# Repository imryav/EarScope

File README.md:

# EarScope — In-Ear Bio-Acoustic Cardiac Monitor (Seeed Studio XIAO RA4M1 Edition)

**EarScope** is an ultra-low-noise, compact hardware and software acquisition platform that captures acoustic and micro-mechanical cardiac biosignals (**PCG**, **SCG**, and **GCG**) directly from an occluded ear canal using standard wired earphones (`3.5 mm` AUX), inspired by *LubDubDecoder (ACM CHI '26)*.

> **Project Engineering Documentation & Hardware Files:**
> * **[Turnkey PCB Fabrication & JLCPCB PCBA Package (`fabrication_files/`)](fabrication_files/)** — Ready-to-order Gerber/Drill ZIP ([`EarScope_XIAO_RA4M1_Gerbers_JLCPCB.zip`](fabrication_files/EarScope_XIAO_RA4M1_Gerbers_JLCPCB.zip)), unpacked RS-274X Gerbers + Excellon Drills, LCSC BOM + CPL CSVs, and ordering guide.
> * **[LTspice Finalization, Verification & Simulation Results](docs/ltspice_simulation_guide.md)** — Validated `3.30 V` cardiac AFE + `1.58 kHz` USB power-supply LPF schematic ([`AFE_Cardiac_5-45Hz.asc`](docs/AFE_Cardiac_5-45Hz.asc) + [`OPA365.lib`](docs/OPA365.lib)), rationale, and verification plots.
> * **[Fabrication-Ready KiCad 8 / 9 Project (`hardware_pcb/EarScope_XIAO_RA4M1/`)](hardware_pcb/EarScope_XIAO_RA4M1/)** — Complete editable schematic (`.kicad_sch`), `100%` routed `48.0 × 20.0 mm` 2-layer PCB (`.kicad_pcb`), and custom footprint library (`.pretty`).
> * **[KiCad 8 / 9 Integrated SPICE (`ngspice`) Simulation Guide & 1-Click Testbench](docs/kicad_spice_simulation_guide.md)** — Ready-to-run KiCad SPICE project ([`hardware_pcb/EarScope_SPICE_Sim/`](hardware_pcb/EarScope_SPICE_Sim/) with [`OPA2365_Dual.lib`](hardware_pcb/EarScope_SPICE_Sim/OPA2365_Dual.lib)) + step-by-step `OP`, `AC` Bode, and `TRAN` verification instructions.
> * **[`kicad-happy` Automated Design Review & Fabrication Release Gate (`11/11 PASS`)](docs/kicad_happy_design_review.md)** — Full electrical, Gerber/CAM, DFM (`0` violations), and EMC (`100 / 100`) sign-off via [`aklofas/kicad-happy`](https://github.com/aklofas/kicad-happy).
> * **[KiCad 8 / 9 Schematic & PCB Design Guide](docs/kicad_pcb_design_guide.md)** — Complete symbol/footprint mapping, custom castellated XIAO RA4M1 footprint with underside pad keepout, `48.0 × 20.0 mm` 2-layer layout, `1.58 kHz` USB LPF, `JP1` solder jumper, active `VREF` guard ring, and Gerber export.
> * **[Enclosure & Carrier PCB Co-Design Guide](docs/fusion360_enclosure_guide.md)** — Parametric Fusion 360 snap-fit enclosure co-designed for the `48.0 × 20.0 mm` XIAO RA4M1 carrier PCB.

---

## 1. System Architecture Overview

EarScope converts microscopic tympanic/ear-canal pressure oscillations (`5 Hz – 45 Hz`) into a high-resolution digital stream over **USB-C**:

* **Sensor Input (`3.5 mm` AUX `PJ-320A` + `JP1` SMD Solder Jumper):** Supports standard passive dynamic earphones (`16–32 Ω` voice coil operating in reverse as a zero-bias acoustic transducer via the ear-canal occlusion effect) **and** electret microphone capsules via a compact 2-pad SMD solder jumper (**`JP1: OPEN = EAR / BRIDGE = MIC`**, switching `2.2 kΩ` DC bias from `+3V3_ANA` with zero mechanical switch contact bounce or enclosure side cutout).
* **Cardiac Analog Front-End (`OPA2365` × 2):** Dual ultra-low-noise (`4.5 nV/√Hz`), rail-to-rail CMOS operational amplifiers configured as a breathing-protected `53.2 dB` preamplifier followed by a 4th-order Butterworth `5 Hz – 45 Hz` bandpass filter (`-60 dB/decade` sub-cardiac slope including input coupling).
* **Two-Stage Quiet `3.30 V` Analog Power Island (`1.58 kHz` Pre-LPF + Low-Noise LDO):** Noisy `+5V_USB` power first passes through a dedicated passive RC Low-Pass Filter (**`R13 = 10 Ω`** feeding **`+5V_FILT`** decoupled by **`C9 = 10 µF` || `C13 = 100 nF`**, $f_c = 1.576\text{ kHz}$, providing `~56 dB` high-frequency USB switching rejection at `1 MHz` where LDO PSRR degrades) before `U3` (`MCP1700T-3302E/TT`) regulates a clean **`3.300 V`** analog rail (`+3V3_ANA`) and **`1.650 V`** virtual-ground reference.
* **Thumb-Sized Digital Acquisition & Streaming (`Seeed Studio XIAO RA4M1` / `102010551`):** Powered by the **Renesas `RA4M1`** (`R7FA4M1AB3CFM`, `48 MHz` Arm Cortex-M4F with FPU) in a `21.0 × 17.8 mm` 14-pad castellated SMD footprint, shrinking the carrier PCB by `29.4%` (`48.0 × 20.0 mm`) while sampling at `500 Hz` with a **true 14-bit SAR ADC** (`0–16,383` counts, `1 LSB = 201.4 µV`) and zero Wi-Fi/BLE RF burst interference over onboard **USB-C**.

```text
[Earphones / Mic (3.5mm AUX + JP1)] ---> [Cardiac AFE (OPA2365, 5–45Hz, USB LPF + 3.30V LDO)] ---> [Seeed XIAO RA4M1 14-Bit ADC (Pin D1/A1)] ===(USB-C @ 500Hz)===> [PC / Python UI]
```

---

## 2. Target Physiological Signals

1. **Phonocardiography (PCG):** Audible and sub-audible heart valve closure sounds (`S1` *"Lub"* and `S2` *"Dub"*).
2. **Seismocardiography (SCG) & Gyrocardiography (GCG):** Reconstruction of chest-wall micro-mechanical cardiac vibrations coupled acoustically through the vasculature and skull into the sealed ear canal.
3. **Cardiac Fiducial Timing Landmarks:**
   * **MC** — Mitral Valve Closure
   * **IM** — Isovolumetric Moment
   * **AO** — Aortic Valve Opening
   * **MA** — Maximal Acceleration
   * **RE** — Rapid Ejection

---

## 3. Finalized Analog Front-End (AFE) & Power Filtering Design

The production schematic (`AFE_Cardiac_5-45Hz.asc` & `EarScope_XIAO_RA4M1.kicad_sch`) comprises six tightly coordinated analog and power-conditioning blocks:

### 3.1 USB Power-Supply Noise Low-Pass Filter (`R13`, `C9 || C13`) & `3.30 V` LDO (`U3`)
Laptop and phone USB-C `VBUS` rails carry `100 kHz – 2 MHz` DC-DC buck switching ripple where CMOS LDO pass-element capacitance degrades PSRR. Placing a passive RC Low-Pass Filter (**$R_{13} = 10\text{ }\Omega$** feeding net **`+5V_FILT`** decoupled by **$C_9 = 10\text{ }\mu\text{F}$** in parallel with low-ESL **$C_{13} = 100\text{ nF}$**) ahead of `U3` (`MCP1700T-3302E/TT`) establishes a `1.58 kHz` pre-filter pole:

$$
f_{c,\text{USB}} = \frac{1}{2\pi R_{13} (C_9 + C_{13})} = \frac{1}{2\pi \cdot 10\text{ }\Omega \cdot 10.1\text{ }\mu\text{F}} \approx 1.576\text{ kHz}
$$

* **Negligible Dropout Overhead:** At full AFE + LDO quiescent load (`< 5 mA` on `+3V3_ANA`, `< 0.05 V` drop; `< 0.19 V` even at `18.4 mA`), `+5V_FILT` stays well above `U3`'s `3.48 V` dropout threshold.
* **High-Frequency Attenuation:** Suppresses `100 kHz` switching ripple by `-36 dB` and `1 MHz` spikes by `~56 dB` *before* `U3`, while damping ceramic MLCC input ringing ($Q < 0.3$).

### 3.2 Virtual Ground Buffer (`U2B`)
A symmetric `1%` thin-film divider ($R_{\text{REF1}} = 100\text{ k}\Omega$, $R_{\text{REF2}} = 100\text{ k}\Omega$) filtered by $C_{\text{REF}} = 10\text{ }\mu\text{F}$ ($f_c \approx 0.32\text{ Hz}$ on `U2B+`) establishes a quiet mid-supply reference:

$$
V_{\text{REF}} = V_{\text{CC\_ANA}} \cdot \frac{R_{\text{REF2}}}{R_{\text{REF1}} + R_{\text{REF2}}} = 3.300\text{ V} \cdot \frac{100\text{ k}\Omega}{100\text{ k}\Omega + 100\text{ k}\Omega} = 1.650\text{ V} \quad (\text{14-bit ADC Code } 8192)
$$

### 3.3 Input Coupling, Breathing Motion Pre-Filter (`C_IN = 68 nF`) & `JP1` (`EAR / MIC`) Solder Jumper
In occluded ear canals, slow respiratory pressure waves (`0.2 – 0.4 Hz`) reach **`~5 mV` peak** — more than `15×` stronger than in-ear cardiac `S1/S2` pulses. Setting $C_{\text{IN}} = 68\text{ nF}$ against $R_{\text{BIAS}} = 1\text{ M}\Omega$ creates a passive high-pass corner ahead of Stage 1:

$$
f_{c,\text{in}} = \frac{1}{2\pi R_{\text{BIAS}} C_{\text{IN}}} = \frac{1}{2\pi \cdot 1\text{ M}\Omega \cdot 68\text{ nF}} \approx 2.34\text{ Hz}
$$

This pre-attenuates `0.25 Hz` breathing artifacts by **`8×` (`-18.0 dB`) *before* preamplification**, completely preventing Stage 1 rail saturation while incurring `< 0.07 dB` loss at `18 Hz`. Ahead of $C_{\text{IN}}$, a 2-pad flat SMD solder jumper (**`JP1`**, `SolderJumper-2_P1.3mm_Open`) leaves **`R_MIC = 2.2 kΩ`** completely open by default (**`OPEN = EAR`**) so `0.00 mA` DC flows through `16–32 Ω` passive earphone voice coils, or connects `R_MIC` to `+3V3_ANA` when bridged with a solder bead (**`BRIDGE = MIC`**) to power electret microphone capsules. Eliminating the mechanical switch removes contact resistance drift, BOM cost, and any dust/ESD aperture in the enclosure wall.

### 3.4 Stage 1 Low-Noise Non-Inverting Preamplifier (`U1A`)
Selected production gain uses **$R_G = 220\text{ }\Omega$** with $R_F = 100\text{ k}\Omega$ in parallel with **$C_F = 1\text{ nF}$**:

$$
G_1 = 1 + \frac{R_F}{R_G} = 1 + \frac{100\text{ k}\Omega}{220\text{ }\Omega} = 455.5 \approx 53.2\text{ dB}, \qquad f_{p,\text{EMI}} = \frac{1}{2\pi R_F C_F} \approx 1.59\text{ kHz}
$$

* Balances high SNR for low-impedance passive earphones (`16–32 Ω`) with wide linear headroom (`> 1.38 V` margin to both rails under `5 mV` breathing waves) and rolls off RF/EMI picked up by the earphone cable above `1.59 kHz`.
* Dual `0805` pads (`R2` + unpopulated `R3` `DNP`) allow easy population of `1 kΩ` (`40.1 dB`), `100 Ω` (`60.0 dB`), or fine parallel gain trimming.

### 3.5 Stage 2 (`5 Hz` HPF, `U1B`) & Stage 3 (`45 Hz` LPF, `U2A`)
* **Stage 2 — 2nd-Order Butterworth Sallen-Key HPF (`U1B`):** $C_{1H} = C_{2H} = 1\text{ }\mu\text{F}$, $R_{AH} = 22.6\text{ k}\Omega$ (feedback to `U1B` output), $R_{BH} = 45.3\text{ k}\Omega$ (to `VREF`), $f_c \approx 4.97\text{ Hz}$. Strips Stage 1 amplified DC offset ($V_{\text{OS}} \times 455.5$) and combines with $C_{\text{IN}}$ for `-60 dB/decade` sub-cardiac rejection.
* **Stage 3 — 2nd-Order Butterworth Sallen-Key LPF (`U2A`):** $R_{1L} = R_{2L} = 24.9\text{ k}\Omega$, $C_{AL} = 200\text{ nF}$, $C_{BL} = 100\text{ nF}$ (referenced directly to **`VREF`**), $f_c \approx 45.2\text{ Hz}$.

### 3.6 Stage 4 — 14-Bit SAR ADC Charge-Reservoir Filter
A passive output filter (**$R_{\text{OUT}} = 100\text{ }\Omega$**, **$C_{\text{OUT}} = 100\text{ nF}$** to `GND`, $f_c \approx 15.9\text{ kHz}$) isolates `U2A` from capacitive loading and absorbs switched-capacitor sampling kickback from the Renesas `RA4M1` 14-bit SAR ADC (`< 0.35 LSB` settling error at `500 Hz`).

---

## 4. Validated LTspice Simulation Results

Full SPICE verification instructions and waveforms are available in [`docs/ltspice_simulation_guide.md`](docs/ltspice_simulation_guide.md).

| Parameter | Final Simulated Value (`R_G = 220 Ω`, `C_IN = 68 nF`) |
| :--- | :--- |
| **Analog Supply & XIAO ADC Span (`VCC_ANA` / `AVCC0`)** | `3.300 V` (`1 LSB = 201.4 µV` @ 14-bit) |
| **USB Pre-LDO Power LPF (`R13 = 10 Ω`, `C9 || C13 = 10.1 µF`)** | **`f_c = 1.576 kHz`** (`~56 dB` pre-attenuation @ `1 MHz`) |
| **Quiescent Output (`V(ADC_IN)`)** | `1.650 V` (14-bit ADC center code `8192`) |
| **Net Mid-Band Gain (`@ 18 Hz`)** | **`52.95 dB` (`×444.3`)** |
| **System `-3 dB` Passband** | **`5.34 Hz – 46.12 Hz`** |
| **Breathing Rejection (`@ 0.25 Hz`)** | **`-71.2 dB` relative to passband** (`3,630×` attenuation) |
| **Stage 1 Swing under `5 mV`, `0.25 Hz` Breathing** | `1.408 V – 1.892 V` (**zero clipping**, `> 1.38 V` rail margin) |
| **Integrated Input-Referred Noise (`5–45 Hz`)** | **`0.141 µVrms`** (`63.3 µVrms` = **`0.31 LSBrms`** at `ADC_IN`) |
| **Power-Up Soft-Start Time** | **`~2.3 s`** smooth exponential settling |

---

## 5. Seeed Studio XIAO RA4M1 Interface & Firmware Configuration

### 5.1 Hardware Pin Mapping (`Seeed Studio XIAO RA4M1` / `102010551`)

| Carrier PCB Signal | XIAO RA4M1 Pad | `RA4M1` Pin | Function & Routing Notes |
| :--- | :--- | :--- | :--- |
| **`+5V_USB`** | **`5V`** (Pad `14`, North-West) | `VBUS` (via onboard Schottky) | Feeds `R13` (`10 Ω`) $\rightarrow$ `+5V_FILT` (`C9 || C13`) $\rightarrow$ `U3` `3.30 V` LDO |
| **`GND`** | **`GND`** (Pad `13`, North-West) | `VSS / AVSS0` | Dual immediate `0.6/0.3 mm` stitching vias straight to solid `B.Cu` `GND` plane |
| **`ADC_IN`** | **`D1 / A1`** (Pad `2`, South-West) | `P000 / AN000` | Dedicated 14-bit SAR ADC input (avoids `D0/A0` DAC mux & `D4/D5` I2C); routed `100%` along South edge `> 10.6 mm` away from `+5V_USB` |
| *Internal `3.3 V` Ref* | *(Internal on XIAO)* | `AVCC0 / VREFH0` | XIAO RA4M1 ties `AVCC0`/`VREFH0` internally to its `3.3 V` rail (no external `AREF` pin); use default `AR_DEFAULT` reference |

### 5.2 Reference Seeed Studio XIAO RA4M1 Acquisition Setup (`C++`)

```cpp
#include <Arduino.h>

constexpr uint8_t PIN_CARDIAC_ADC = A1;     // XIAO RA4M1 Pad 2 (D1 / A1 -> P000 / AN000)
constexpr uint32_t SAMPLE_PERIOD_US = 2000; // 500 Hz exact sampling rate

void setup() {
  Serial.begin(230400);
  // Note: Seeed Studio XIAO RA4M1 ties AVCC0/VREFH0 internally to 3.3 V (default AR_DEFAULT).
  analogReadResolution(14); // Enable true 14-bit SAR resolution (0 .. 16383, mid = 8192)
}

void loop() {
  static uint32_t lastSampleUs = 0;
  uint32_t nowUs = micros();
  if (nowUs - lastSampleUs >= SAMPLE_PERIOD_US) {
    lastSampleUs += SAMPLE_PERIOD_US;
    uint16_t raw14 = analogRead(PIN_CARDIAC_ADC);
    Serial.println(raw14);
  }
}
```

---

## 6. Fabrication-Ready KiCad 8 / 9 Carrier PCB (`Rev 2.0`) & `kicad-happy` Verification (`PASS`)

The editable KiCad 8/9 source project lives in [`hardware_pcb/EarScope_XIAO_RA4M1/`](hardware_pcb/EarScope_XIAO_RA4M1/), while the ready-to-order manufacturing package lives in [`fabrication_files/`](fabrication_files/). All design and CAM files passed **`11 / 11` strict automated release-gate checks** in [`aklofas/kicad-happy`](https://github.com/aklofas/kicad-happy) (full audit in [`docs/kicad_happy_design_review.md`](docs/kicad_happy_design_review.md)):

* **Compact Form Factor & Underside Keepout:** Shrunk by **`29.4%`** to **`48.0 × 20.0 × 1.6 mm`** (`960 mm²`) with a dedicated `Keepout_XIAO_Underside_Pads` (`[0.95..16.90] × [4.00..16.10] mm`) blocking all `F.Cu` copper and vias beneath the XIAO RA4M1's 16 exposed underside pads (`BAT+/BAT-`, SWD, CAN, etc.).
* **Routing & Parity:** `30 / 30` PCB nets `100%` routed (`0` unrouted nets, `0` cross-analysis findings, `262` segments, `33` vias including `17` `GND` stitching vias over an unbroken `B.Cu` `GND` plane), with `+5V_USB` isolated along the North edge and `/ADC_IN` along the South edge (`> 10.6 mm` separation, zero crossings).
* **DFM & Clearances:** **`standard` (`$2`) 2-layer tier** with **`0` geometric DRC/DFM violations**, `0` courtyard overlaps, and `0` keepout violations (`min_track = 0.25 mm`, `min_drill = 0.30 mm`, `min_annular_ring = 0.15 mm`).
* **Gerber & Drill CAM Audit:** **`0` findings (`Complete`)** — all `9/9` RS-274X (X2) Gerber layers + `PTH.drl` (including routed `0.6 × 1.5 mm` oval slots for `J1`) + `NPTH.drl` + `.gbrjob` bundled in [`EarScope_XIAO_RA4M1_Gerbers_JLCPCB.zip`](fabrication_files/EarScope_XIAO_RA4M1_Gerbers_JLCPCB.zip).
* **EMC & ESD Sign-Off:** **`100 / 100` EMC score (`0` errors, `0` warnings)** — `1.58 kHz` pre-LDO USB power LPF (`R13 + C9 || C13`), bidirectional ESD diode **`D1` (`PESD3V3L1BA`, `SOD-323`)** right at `J1` (`PJ-320A`), local `100 nF` decoupling (`C11, C12`) `< 2 mm` from `U1` and `U2`, and active `VREF` guard ring around `U1A+`.
* **Turnkey PCBA Outputs:** Ready-to-upload [`EarScope_JLCPCB_BOM.csv`](fabrication_files/EarScope_JLCPCB_BOM.csv) (`19` LCSC lines / `30` SMD parts, including JLCPCB Basic resistor `R13 = 10 Ω` `C17415`) and [`EarScope_JLCPCB_CPL.csv`](fabrication_files/EarScope_JLCPCB_CPL.csv) (`30` placement rows; `A1` XIAO RA4M1 hand-soldered flush via 14 castellated pads; `JP1` bare copper solder jumper).

---

## 7. Production Bill of Materials (BOM)

All passive components use **`0805` SMD** packages for straightforward hand soldering or turnkey PCBA (`JLCPCB` / `PCBWay`).

| Designator | Value / Part Number | Package / Footprint | Qty | Engineering Notes |
| :--- | :--- | :--- | :---: | :--- |
| **A1 (MCU)** | `Seeed Studio XIAO RA4M1` (`102010551`) | Castellated SMD (`2×7`, `21.0 × 17.8 mm`) | 1 | Flush-mounted via 14 castellated pads (`F.Cu`/via keepout under 16 belly pads); USB-C |
| **U1, U2** | `OPA2365AIDR` | SOIC-8 | 2 | Dual `4.5 nV/√Hz`, zero-crossover rail-to-rail CMOS op-amp |
| **U3** | `MCP1700T-3302E/TT` | SOT-23-3 | 1 | Low-noise `3.30 V` LDO fed from filtered `+5V_FILT`, powering `+3V3_ANA` (`VCC_ANA`) |
| **D1** | `PESD3V3L1BA` | SOD-323 | 1 | Low-capacitance bidirectional `3.3 V` ESD clamp on `J1` (`VIN_RAW`, LCSC `C15772`) |
| **J1** | `PJ-320A` (3.5 mm TRRS) | `TRRS-PJ-320A` (`12.1 × 6.1 × 5.0 mm`) | 1 | Earphone / headset AUX input receptacle (`Tip` = signal, `Ring2+Sleeve` = `GND`) |
| **JP1** | `SolderJumper_2_Open` (PCB Copper) | `SolderJumper-2_P1.3mm_Open` (`1.0×1.5 mm` pads) | (PCB) | Zero-cost 2-pad SMD solder jumper (`OPEN = EAR` `0 V` DC; `BRIDGE = MIC` `+3V3_ANA` bias; no `F.Paste`) |
| **R13 (`R_LPF`)** | `10 Ω` (`1%`, `0805W8F100JT5E`) | 0805 (LCSC `C17415` Basic) | 1 | `1.58 kHz` USB power-supply LPF series resistor (`+5V_USB` $\rightarrow$ `+5V_FILT`) |
| **C9, C13** | `10 µF` (`C15850`) + `100 nF` (`C49678`) | 0805 (`X5R/X7R`) | 1 + 1 | Parallel bulk + HF ceramic LPF bank on `+5V_FILT` ahead of `U3` (`f_c = 1.576 kHz`) |
| **C8, C10** | `10 µF` (`CL21A106KAYNNNE`) | 0805 (`X5R/X7R`, `25 V`, `C15850`) | 2 | `C8` filters `VREF_DIV` (`U2B+`); `C10` stabilizes `U3` `+3V3_ANA` LDO output |
| **C1 (`C_IN`)** | `68 nF` | 0805 (`X7R`/`C0G`, `50 V`, `C53085`) | 1 | `2.34 Hz` breathing pre-filter ahead of `U1A+` |
| **C2 (`C_F`)** | `1 nF` | 0805 (`C0G/NP0`, `50 V`, `C1588`) | 1 | Stage 1 feedback HF/EMI roll-off (`1.59 kHz`) across `R4` |
| **C3, C4 (`C_1H, C_2H`)** | `1 µF` | 0805 (`X7R`, `50 V`, `C28323`) | 2 | Stage 2 `5 Hz` Sallen-Key HPF capacitors |
| **C5 (`C_AL`)** | `220 nF` / `200 nF` | 0805 (`X7R`, `50 V`, `C315201`) | 1 | Stage 3 `45 Hz` Sallen-Key LPF feedback capacitor |
| **C6, C7 (`C_BL, C_OUT`)** | `100 nF` | 0805 (`X7R`, `50 V`, `C49678`) | 2 | `C6` tied to **`VREF`**; `C7` SAR ADC charge reservoir tied to **`GND`** near `A1` `D1/A1` |
| **C11, C12** | `100 nF` | 0805 (`X7R`, `50 V`, `C49678`) | 2 | Local `+3V3_ANA` bypass (`< 2 mm`) on `U1` and `U2` |
| **R4–R6 (`R_F, R_REF1/2`)** | `100 kΩ` (`1%`) | 0805 (`C149504`) | 3 | Stage 1 feedback resistor and symmetric `1.650 V` divider |
| **R1 (`R_BIAS`)** | `1 MΩ` (`1%`) | 0805 (`C17514`) | 1 | Input DC bias reference to `VREF` |
| **R2 (`R_G`), R3 (`DNP`)** | `220 Ω` (`1%`, `C17557`) + `DNP` pad | 0805 | 1 + 1 | Selected Stage 1 gain (`×455.5` / `53.2 dB`) + parallel trim footprint |
| **R7, R8 (`R_AH, R_BH`)** | `22.6 kΩ` (`C17562`), `45.3 kΩ` (`C25900`) | 0805 (`1%`) | 1 ea | Stage 2 `5 Hz` Butterworth Sallen-Key HPF resistors |
| **R9, R10 (`R_1L, R_2L`)** | `24.9 kΩ` (`1%`) | 0805 (`C17590`) | 2 | Stage 3 `45 Hz` Butterworth Sallen-Key LPF resistors |
| **R11 (`R_OUT`)** | `100 Ω` (`1%`) | 0805 (`C17407`) | 1 | Isolates `U2A` output from `C7` SAR charge reservoir |
| **R12 (`R_MIC`)** | `2.2 kΩ` (`1%`) | 0805 (`C17520`) | 1 | Electret capsule bias pull-up in series with `JP1` (`+3V3_ANA` side) |

---

## 8. Repository Structure

```text
EarScope/
├── README.md                                       # Main system architecture, BOM & results
├── fabrication_files/                              # Ready-to-order PCB & PCBA manufacturing package (Rev 2.0)
│   ├── README.md                                   # JLCPCB / PCBWay ordering, XIAO soldering & JP1 guide
│   ├── EarScope_XIAO_RA4M1_Gerbers_JLCPCB.zip      # Single-upload Gerber RS-274X + Excellon Drill ZIP
│   ├── EarScope_JLCPCB_BOM.csv                     # Turnkey LCSC SMT Bill of Materials (19 lines / 30 parts)
│   ├── EarScope_JLCPCB_CPL.csv                     # Turnkey Pick-and-Place coordinates (mm, Top side)
│   ├── EarScope_Master_BOM.csv                     # Full 31-part engineering BOM (incl. Seeed XIAO RA4M1)
│   ├── EarScope_AliExpress_BOM.csv                 # DIY AliExpress ordering BOM with links & USD/ILS pricing
│   └── gerbers/                                    # Unpacked .gbr, .drl & .gbrjob CAM layers
├── docs/
│   ├── AFE_Cardiac_5-45Hz.asc                      # Finalized LTspice schematic (XIAO RA4M1 + USB Power LPF)
│   ├── OPA365.lib                                  # Texas Instruments OPA365 / OPA2365 SPICE macro-model
│   ├── ltspice_simulation_guide.md                 # LTspice verification guide & benchmark results
│   ├── kicad_spice_simulation_guide.md             # KiCad 8/9 integrated ngspice simulation guide
│   ├── kicad_pcb_design_guide.md                   # Step-by-step KiCad 8/9 schematic, PCB layout & Gerber guide
│   ├── kicad_happy_design_review.md                # Automated kicad-happy PCB review & PASS release gate report
│   ├── fusion360_enclosure_guide.md                # Parametric 3D enclosure & 48×20 mm PCB co-design guide
│   └── figures/                                    # Verification waveforms & PCB layout SVG diagrams
│       ├── afe_bode_response.svg
│       ├── cin_preamp_saturation_comparison.svg
│       ├── transient_startup_and_cardiac_output.svg
│       ├── input_referred_noise_spectrum.svg
│       ├── kicad_pcb_floorplan.svg
│       └── earscope_routed_pcb.svg
└── hardware_pcb/
    ├── EarScope_XIAO_RA4M1/                        # Editable KiCad 8/9 manufacturing project (Rev 2.0)
    │   ├── EarScope_XIAO_RA4M1.kicad_pro
    │   ├── EarScope_XIAO_RA4M1.kicad_sch           # 0 ERC warnings, 31 BOM parts + JP1 + TP1–TP6
    │   ├── EarScope_XIAO_RA4M1.kicad_pcb           # 48.0 × 20.0 mm 2-layer 100% routed carrier PCB
    │   ├── fp-lib-table
    │   ├── EarScope_Footprints.pretty/             # 9 custom/verified SMD footprints (.kicad_mod)
    │   └── bom/                                    # Source BOM & CPL exports
    └── EarScope_SPICE_Sim/                         # Standalone KiCad 8/9 ngspice AFE + USB LPF testbench
```

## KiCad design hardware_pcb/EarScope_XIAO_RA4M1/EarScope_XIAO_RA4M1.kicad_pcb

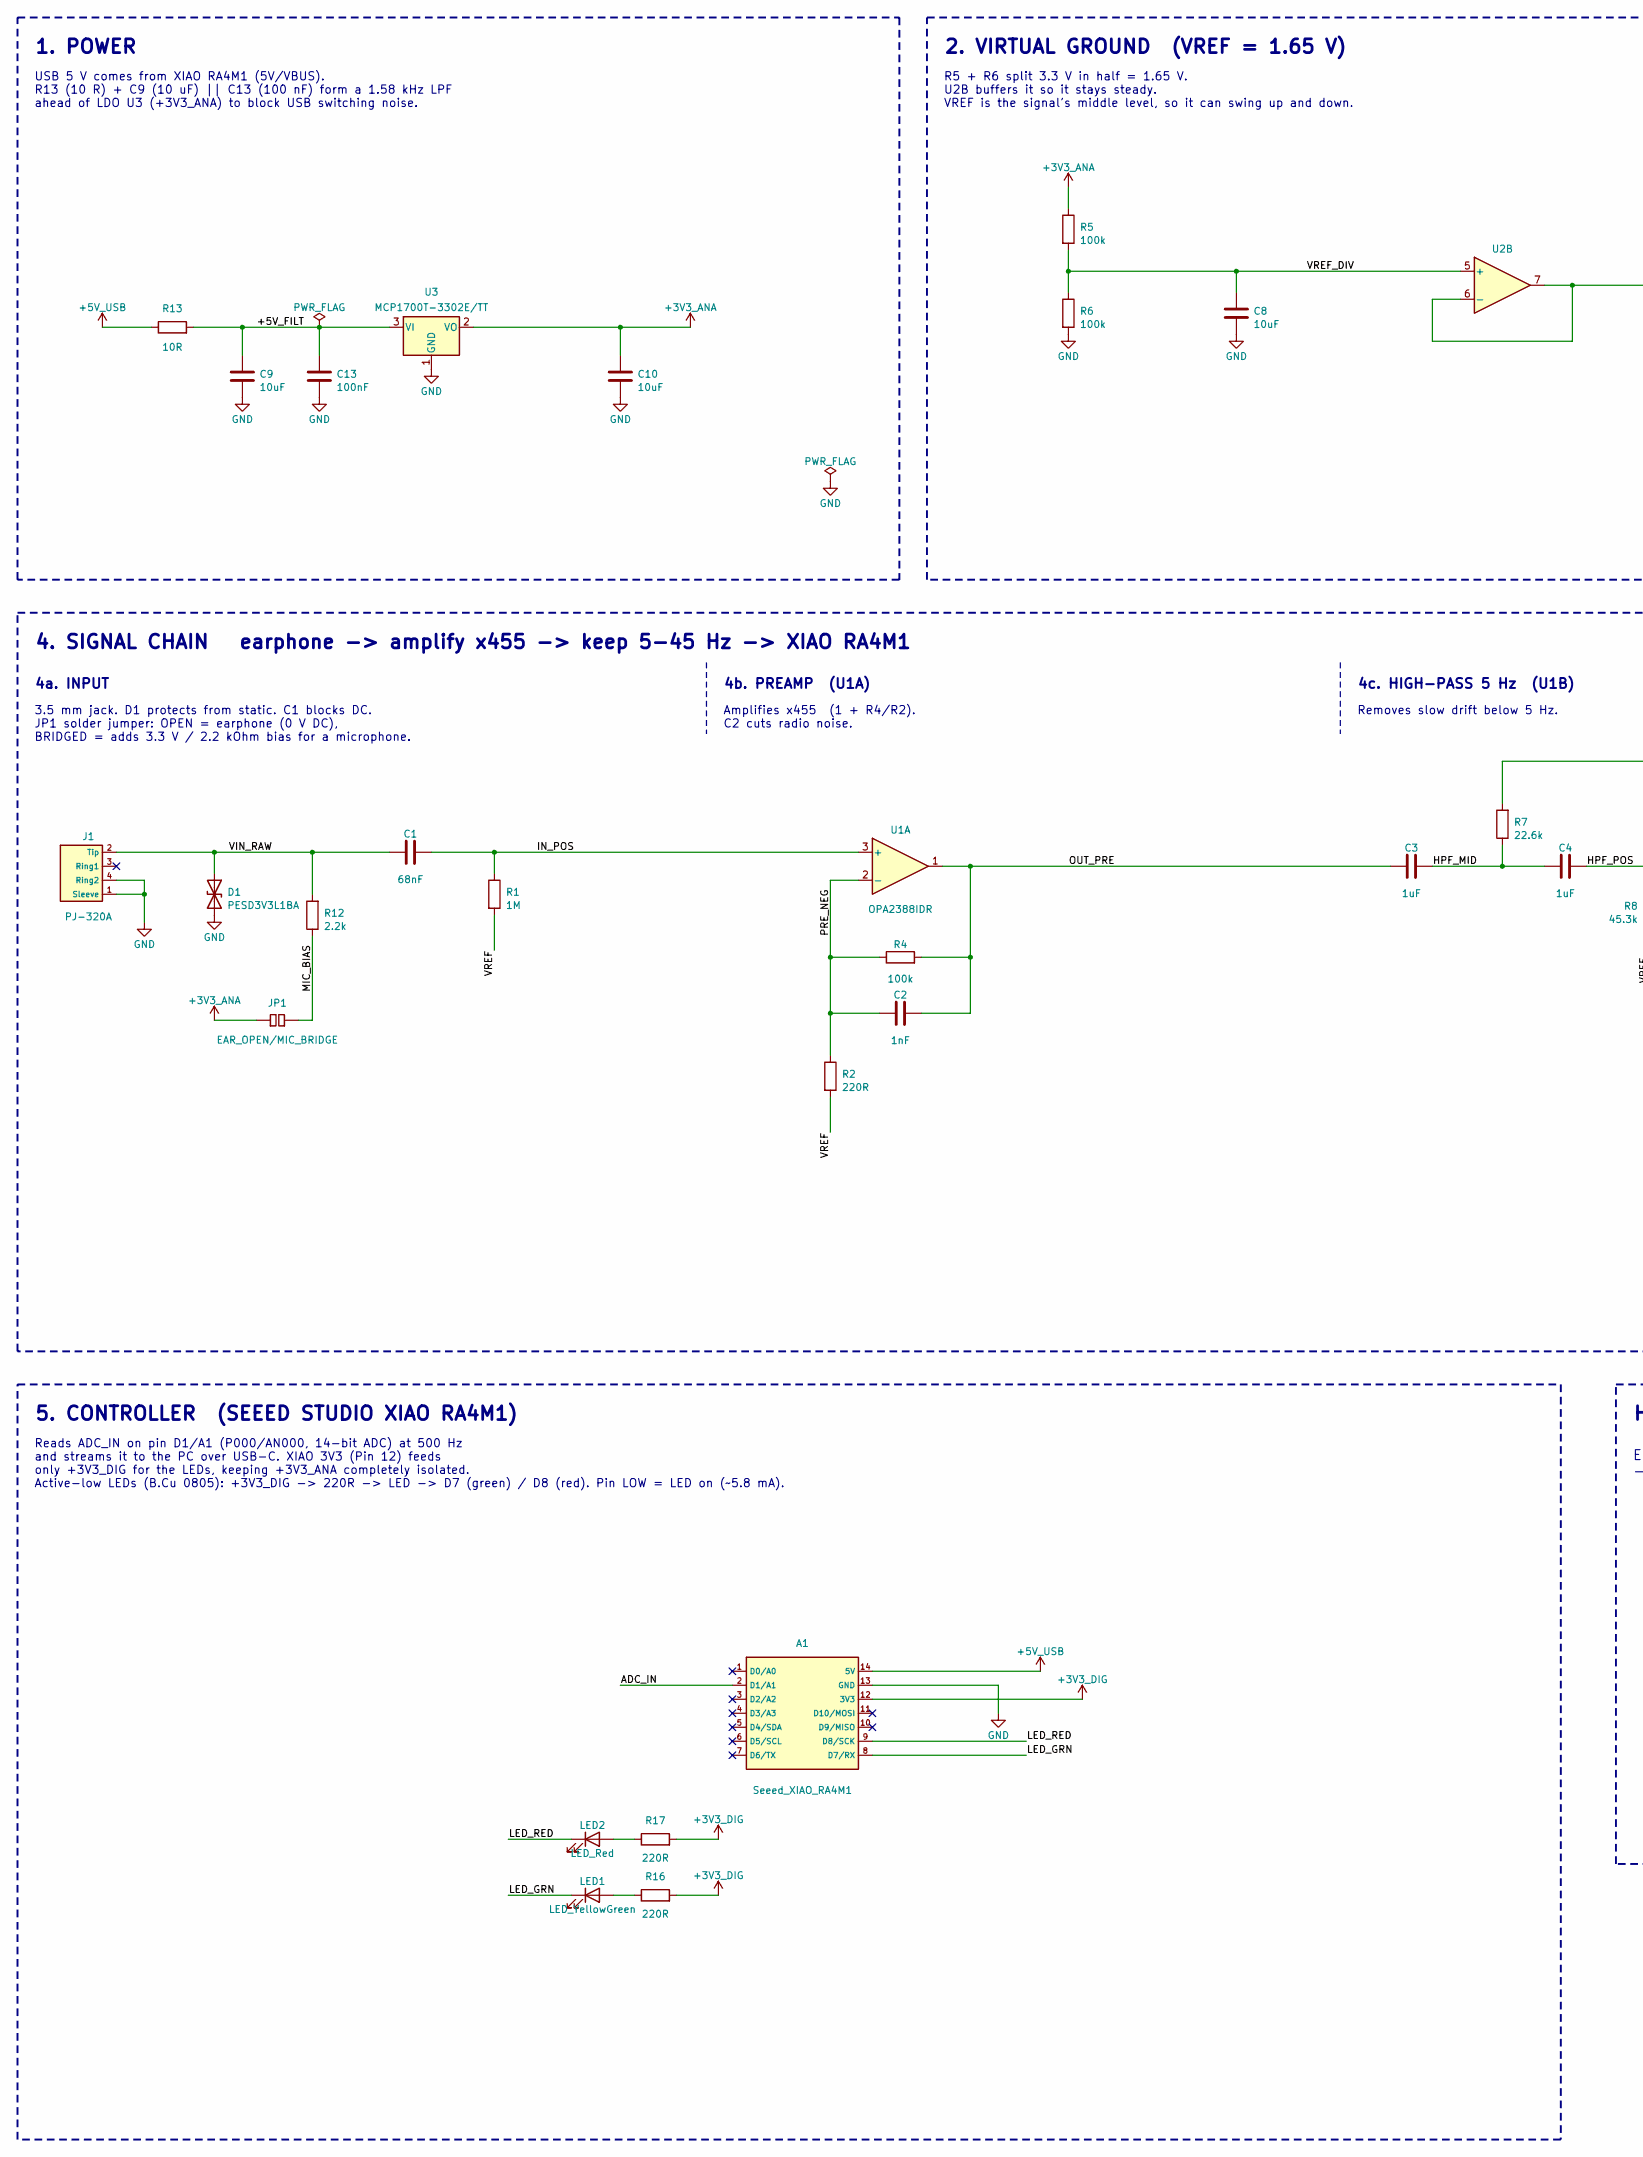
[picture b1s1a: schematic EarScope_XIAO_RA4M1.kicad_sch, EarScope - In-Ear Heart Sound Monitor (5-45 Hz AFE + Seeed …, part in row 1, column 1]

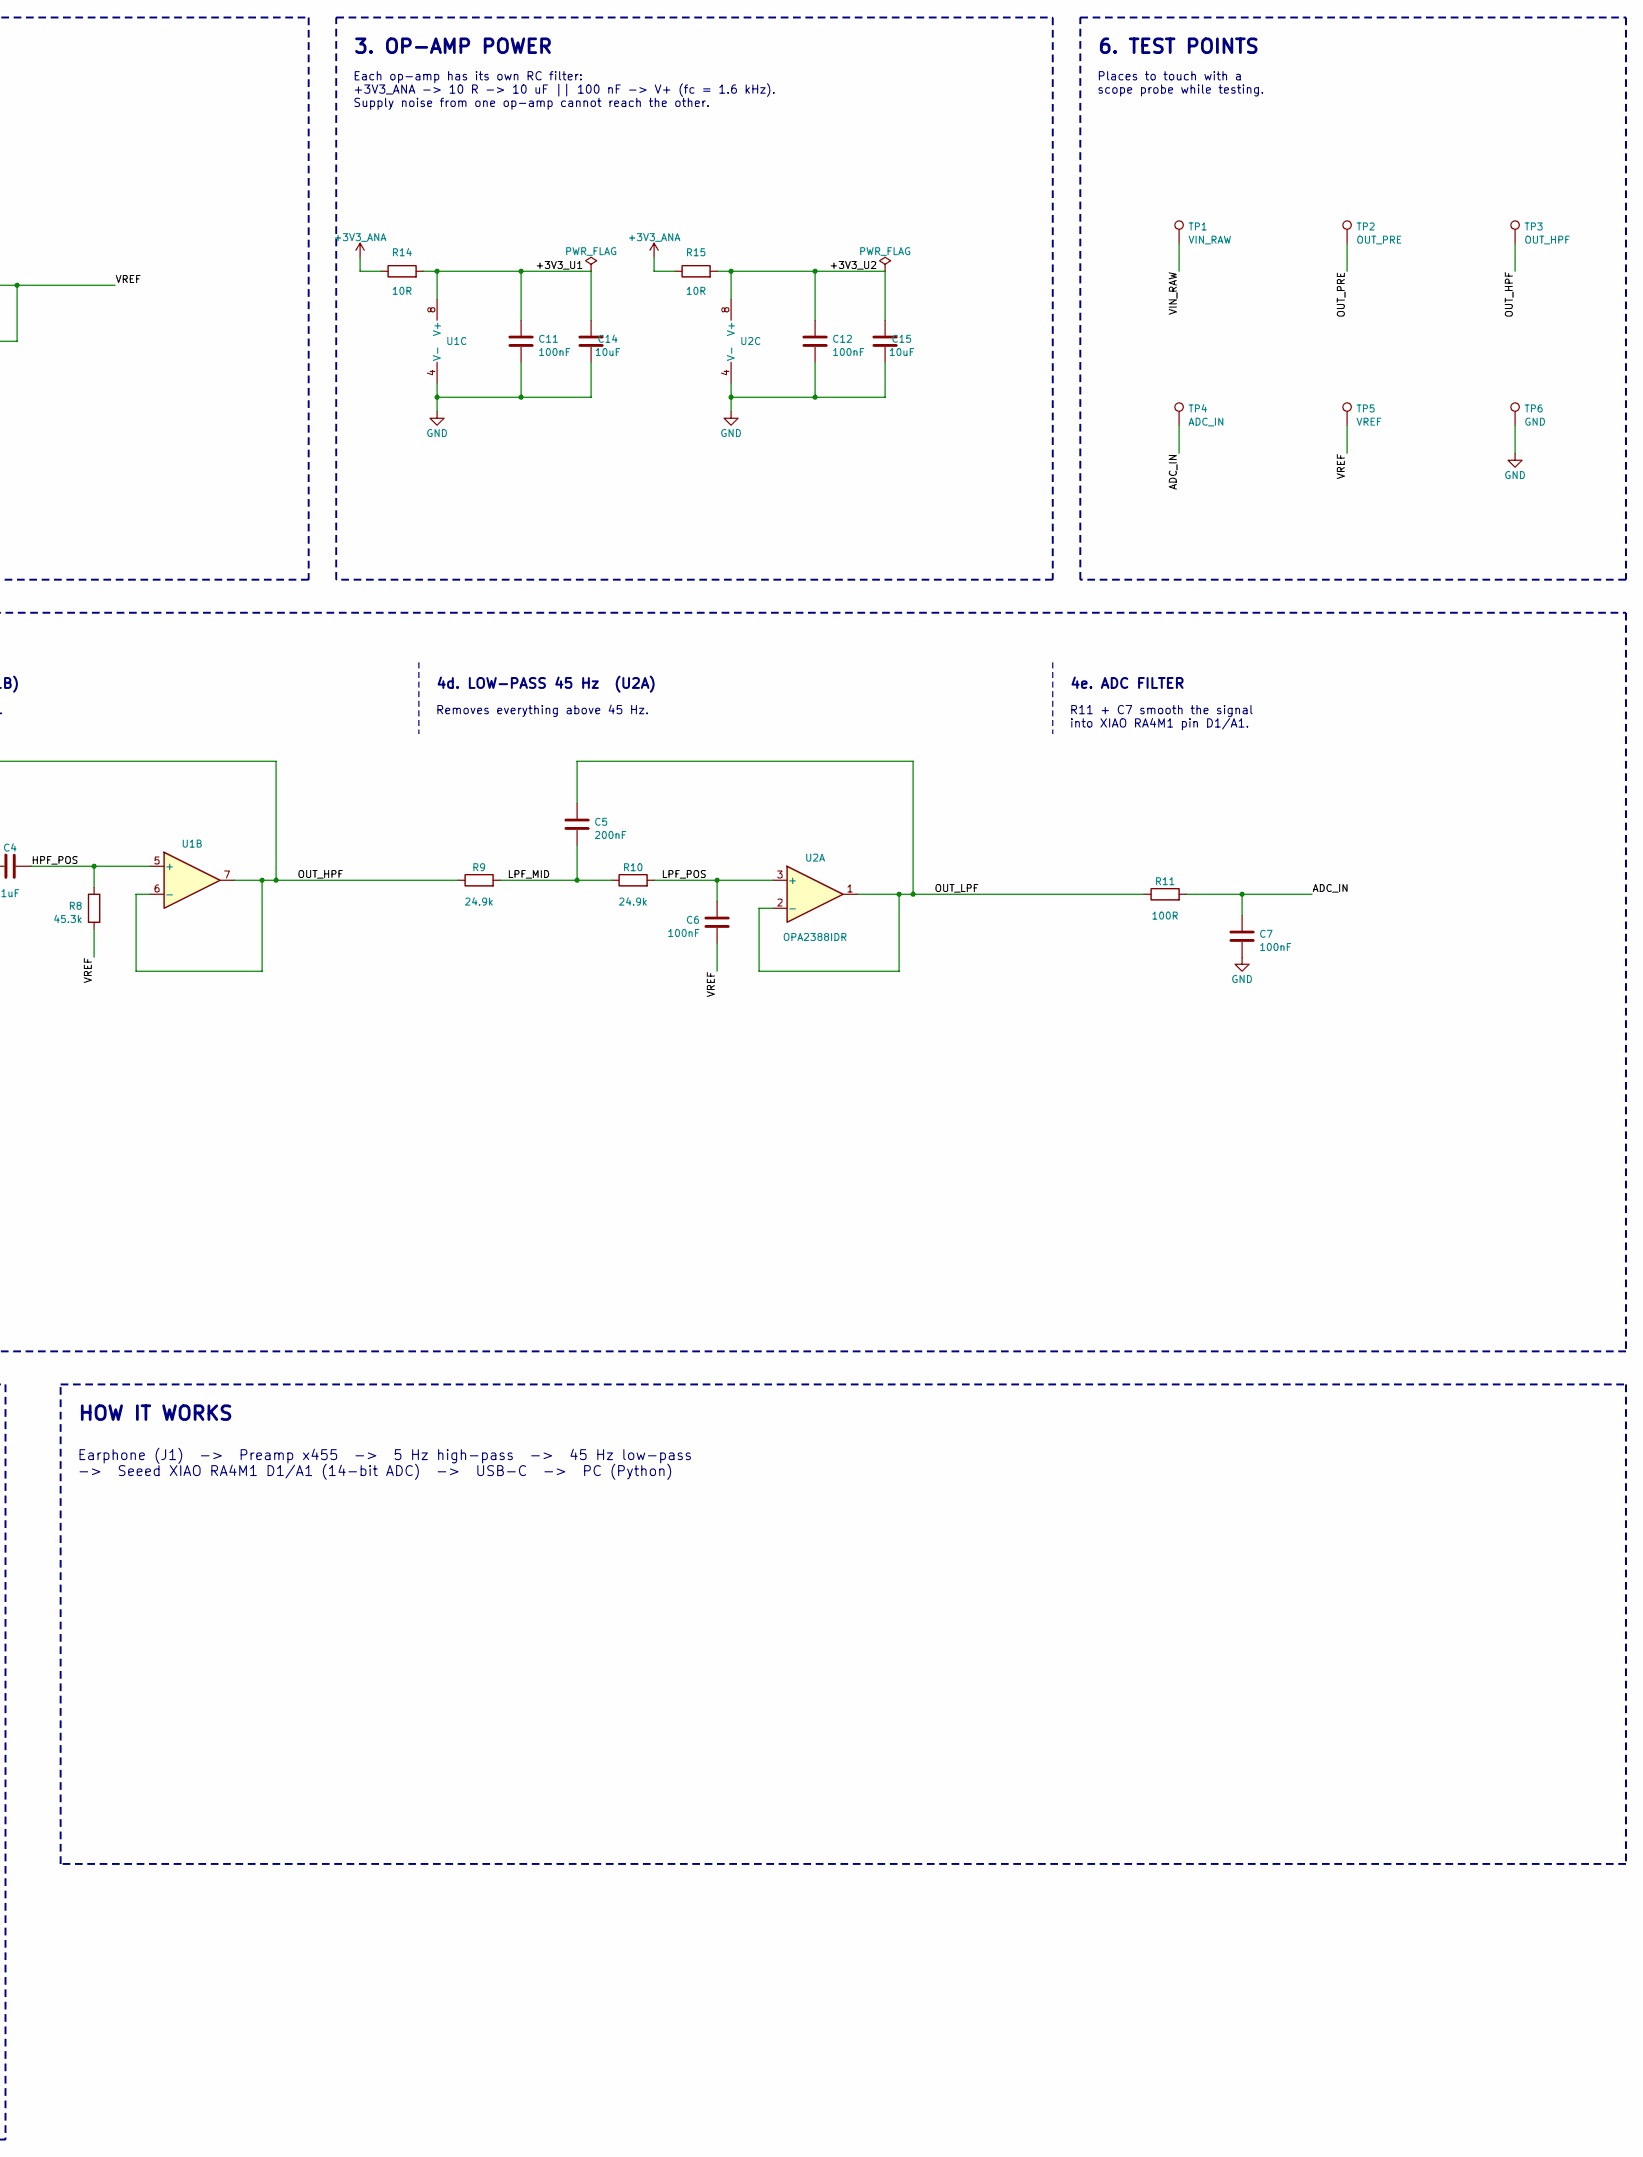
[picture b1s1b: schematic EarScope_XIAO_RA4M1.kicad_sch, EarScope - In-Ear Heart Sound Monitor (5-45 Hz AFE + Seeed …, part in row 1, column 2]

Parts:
A1: Seeed_XIAO_RA4M1; Seeed_XIAO_RA4M1_Castellated_SMD; MPN 102010551
C1: 68nF; C_0805_2012Metric; MPN GCM21BR71H683KA37L; LCSC C1589
C2: 1nF; C_0805_2012Metric; MPN GRM2165C1H102JA01D; LCSC C1706
C3, C4: 1uF; C_0805_2012Metric; MPN CL21B105KBFNNNE; LCSC C28323
C5: 200nF; C_0805_2012Metric; MPN GCM21BR71H224KA37L; LCSC C53438
C6, C7, C11, C12, C13: 100nF; C_0805_2012Metric; MPN CL21B104KBCNNNC; LCSC C49678
C8, C9, C10, C14, C15: 10uF; C_0805_2012Metric; MPN CL21A106KAYNNNE; LCSC C15850
D1: PESD3V3L1BA; SOD-323; MPN PESD3V3L1BA,115; LCSC C15772
J1: PJ-320A; TRRS-PJ-320A; MPN PJ-320A; LCSC C2884926
JP1: EAR_OPEN/MIC_BRIDGE; SolderJumper-2_P1.3mm_Open_RoundedPad1.0x1.5mm
LED1: LED_YellowGreen; LED_0805_2012Metric; MPN KT-0805YG; LCSC C2292
LED2: LED_Red; LED_0805_2012Metric; MPN KT-0805R; LCSC C2295
R1: 1M; R_0805_2012Metric; MPN RC0805FR-071ML; LCSC C17514
R2, R16, R17: 220R; R_0805_2012Metric; MPN RC0805FR-07220RL; LCSC C17557
R4, R5, R6: 100k; R_0805_2012Metric; MPN RC0805FR-07100KL; LCSC C17407
R7: 22.6k; R_0805_2012Metric; MPN RC0805FR-0722K6L; LCSC C137927
R8: 45.3k; R_0805_2012Metric; MPN RC0805FR-0745K3L; LCSC C138044
R9, R10: 24.9k; R_0805_2012Metric; MPN RC0805FR-0724K9L; LCSC C25962
R11: 100R; R_0805_2012Metric; MPN RC0805FR-07100RL; LCSC C17408
R12: 2.2k; R_0805_2012Metric; MPN RC0805FR-072K2L; LCSC C17520
R13, R14, R15: 10R; R_0805_2012Metric; MPN 0805W8F100JT5E; LCSC C17415
TP1: VIN_RAW; TestPoint_Pad_D1.2mm
TP2: OUT_PRE; TestPoint_Pad_D1.2mm
TP3: OUT_HPF; TestPoint_Pad_D1.2mm
TP4: ADC_IN; TestPoint_Pad_D1.2mm
TP5: VREF; TestPoint_Pad_D1.2mm
TP6: GND; TestPoint_Pad_D1.2mm
U1, U2: OPA2388IDR; SOIC-8_3.9x4.9mm_P1.27mm; MPN OPA2388IDR
U3: MCP1700T-3302E/TT; SOT-23; MPN MCP1700T-3302E/TT; LCSC C39051

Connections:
+3V3_ANA: C10.1, JP1.1 (A), R5.1, R14.1, R15.1, U3.2 (VO)
+3V3_DIG: A1.12 (3V3), R16.2, R17.2
+5V_USB: A1.14 (5V), R13.1
/+3V3_U1: C11.1, C14.1, R14.2, U1.8 (V+)
/+3V3_U2: C12.1, C15.1, R15.2, U2.8 (V+)
/+5V_FILT: C9.1, C13.1, R13.2, U3.3 (VI)
/ADC_IN: A1.2 (D1/A1), C7.1, R11.2, TP4.1 (1_1)
/HPF_MID: C3.2, C4.1, R7.1
/HPF_POS: C4.2, R8.1, U1.5 (+)
/IN_POS: C1.2, R1.1, U1.3 (+)
/LED_GRN: A1.8 (D7/RX), LED1.1 (K)
/LED_RED: A1.9 (D8/SCK), LED2.1 (K)
/LPF_MID: C5.1, R9.2, R10.1
/LPF_POS: C6.1, R10.2, U2.3 (+)
/MIC_BIAS: JP1.2 (B), R12.1
/OUT_HPF: R7.2, R9.1, TP3.1 (1_1), U1.6 (-), U1.7
/OUT_LPF: C5.2, R11.1, U2.1, U2.2 (-)
/OUT_PRE: C2.2, C3.1, R4.2, TP2.1 (1_1), U1.1
/PRE_NEG: C2.1, R2.1, R4.1, U1.2 (-)
/VIN_RAW: C1.1, D1.1 (A1), J1.2 (Tip), R12.2, TP1.1 (1_1)
/VREF: C6.2, R1.2, R2.2, R8.2, TP5.1 (1_1), U2.6 (-), U2.7
/VREF_DIV: C8.1, R5.2, R6.1, U2.5 (+)
GND: A1.13 (GND), C7.2, C8.2, C9.2, C10.2, C11.2, C12.2, C13.2, C14.2, C15.2, D1.2 (A2), J1.1 (Sleeve), J1.4 (Ring2), R6.2, TP6.1 (1_1), U1.4 (V-), U2.4 (V-), U3.1 (GND)
unnamed: LED1.2 (A), R16.1
unnamed: LED2.2 (A), R17.1

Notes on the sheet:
1. POWER
USB 5 V comes from XIAO RA4M1 (5V/VBUS). R13 (10 R) + C9 (10 uF) || C13 (100 nF) form a 1.58 kHz LPF ahead of LDO U3 (+3V3_ANA) to block USB switching noise.
2. VIRTUAL GROUND (VREF = 1.65 V)
R5 + R6 split 3.3 V in half = 1.65 V. U2B buffers it so it stays steady. VREF is the signal's middle level, so it can swing up and down.
3. OP-AMP POWER
Each op-amp has its own RC filter: +3V3_ANA -> 10 R -> 10 uF || 100 nF -> V+ (fc = 1.6 kHz). Supply noise from one op-amp cannot reach the other.
6. TEST POINTS
Places to touch with a scope probe while testing.
4. SIGNAL CHAIN earphone -> amplify x455 -> keep 5-45 Hz -> XIAO RA4M1
4a. INPUT
3.5 mm jack. D1 protects from static. C1 blocks DC. JP1 solder jumper: OPEN = earphone (0 V DC), BRIDGED = adds 3.3 V / 2.2 kOhm bias for a microphone.
4b. PREAMP (U1A)
Amplifies x455 (1 + R4/R2). C2 cuts radio noise.
4c. HIGH-PASS 5 Hz (U1B)
Removes slow drift below 5 Hz.
4d. LOW-PASS 45 Hz (U2A)
Removes everything above 45 Hz.
4e. ADC FILTER
R11 + C7 smooth the signal into XIAO RA4M1 pin D1/A1.
5. CONTROLLER (SEEED STUDIO XIAO RA4M1)
Reads ADC_IN on pin D1/A1 (P000/AN000, 14-bit ADC) at 500 Hz and streams it to the PC over USB-C. XIAO 3V3 (Pin 12) feeds only +3V3_DIG for the LEDs, keeping +3V3_ANA completely isolated. Active-low LEDs (B.Cu 0805): +3V3_DIG -> 220R -> LED -> D7 (green) / D8 (red). Pin LOW = LED on (~5.8 mA).
HOW IT WORKS
Earphone (J1) -> Preamp x455 -> 5 Hz high-pass -> 45 Hz low-pass -> Seeed XIAO RA4M1 D1/A1 (14-bit ADC) -> USB-C -> PC (Python)

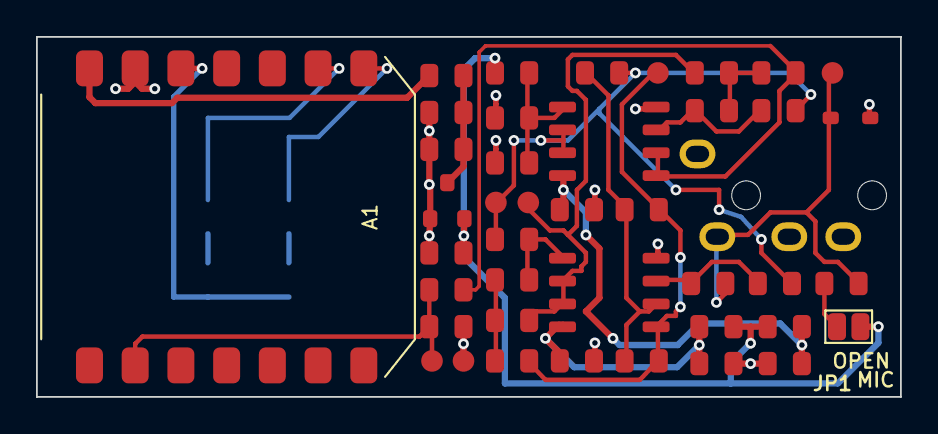
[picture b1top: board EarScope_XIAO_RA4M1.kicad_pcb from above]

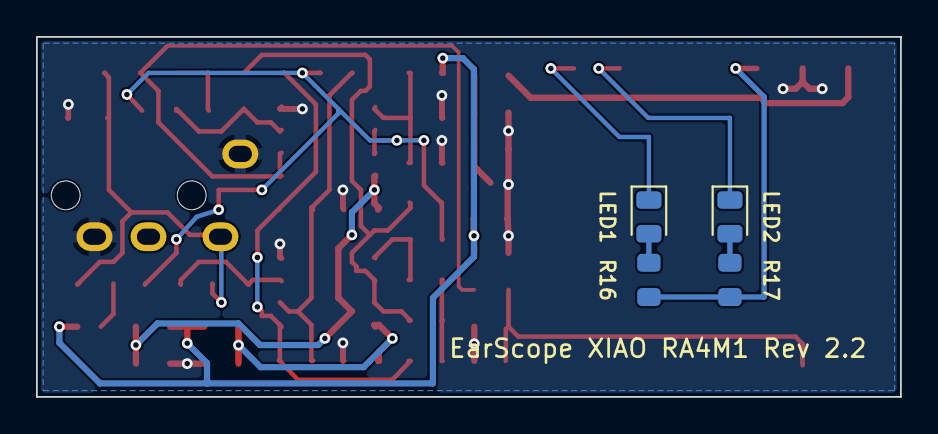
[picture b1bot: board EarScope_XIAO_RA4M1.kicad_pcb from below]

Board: 2 copper layers, 48.0 x 20.0 mm, 46 parts (4 on the bottom side), 25 nets.

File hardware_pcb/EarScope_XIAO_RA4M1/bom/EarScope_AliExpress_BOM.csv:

Reference,Qty_Per_Board,Value_Spec,Package_Footprint,MPN_Marking,AliExpress_Search_Terms,AliExpress_Order_URL,Typical_Pack_Qty,Est_Pack_Price_USD,Est_Cost_Per_Board_USD,Est_Pack_Price_ILS,Notes_And_Alternatives
A1,1,Seeed Studio XIAO RA4M1,Castellated SMD (21x17.8mm),102010551,Seeed Studio XIAO RA4M1,https://www.aliexpress.com/w/wholesale-Seeed-Studio-XIAO-RA4M1.html,1,5.90,5.90,21.85,"Choose UN-SOLDERED (without pin headers) for flush SMD mounting; official Seeed page ($4.99): https://www.seeedstudio.com/Seeed-XIAO-RA4M1-p-5943.html"
"U1,U2",2,OPA2388IDR Dual Zero-Drift Op-Amp,SOIC-8 / SOP-8 (1.27mm pitch),OPA2388IDR,OPA2388IDR SOP-8,https://www.aliexpress.com/w/wholesale-OPA2388IDR-SOP-8.html,,,,,"Price not estimated yet. Verify SOIC-8 / SOP-8 (not MSOP-8 / VSSOP); prefer genuine TI from Mouser / DigiKey. OPA2365AIDR is a pin-compatible backup"
U3,1,MCP1700T-3302E/TT 3.3V LDO,SOT-23-3,MCP1700T-3302E/TT (3302E),MCP1700T-3302E SOT-23,https://www.aliexpress.com/w/wholesale-MCP1700T-3302E-SOT-23.html,10,1.80,0.18,6.65,"Verify 3.3V fixed output (3302E) in SOT-23-3 SMD package (do NOT order TO-92 through-hole MCP1700-3302E/TO)"
D1,1,PESD3V3L1BA 3.3V ESD TVS,SOD-323,PESD3V3L1BA,PESD3V3L1BA SOD-323,https://www.aliexpress.com/w/wholesale-PESD3V3L1BA-SOD-323.html,20,1.20,0.06,4.45,"Bidirectional 3.3V low-capacitance ESD diode in SOD-323 package"
J1,1,PJ-320A 3.5mm TRRS Audio Jack,SMD 4-Pole TRRS + Locating Pegs,PJ-320A,PJ-320A 3.5mm 4 pole jack,https://www.aliexpress.com/w/wholesale-PJ-320A-3.5mm-4-pole.html,10,1.50,0.15,5.55,"4-pin TRRS 3.5mm headphone jack with 2 bottom plastic alignment pegs (example listing: https://www.aliexpress.com/item/33029465106.html)"
C1,1,68nF 50V X7R 10%,0805,68nF (683) 0805 X7R,0805 68nF 683 X7R capacitor 100pcs,https://www.aliexpress.com/w/wholesale-0805-68nF-683-X7R-cap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,100,1.10,0.01,4.05,"Stage 1 AC coupling HPF capacitor (fc = 2.34 Hz)"
C2,1,1nF 50V C0G/NP0 5%,0805,1nF (102) 0805 NP0 C0G,0805 1nF 102 NPO C0G capacitor 100pcs,https://www.aliexpress.com/w/wholesale-0805-1nF-102-NPO-C0G-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,100,1.10,0.01,4.05,"Select C0G / NP0 dielectric for low-distortion Stage 1 feedback roll-off"
"C3,C4",2,1uF 25V/50V X7R 10%,0805,1uF (105) 0805 X7R,0805 1uF 105 X7R capacitor 100pcs,https://www.aliexpress.com/w/wholesale-0805-1uF-105-X7R-capa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,100,1.20,0.02,4.45,"Stage 2 5 Hz Sallen-Key Butterworth HPF capacitors"
C5,1,200nF (or 220nF) 50V X7R 10%,0805,200nF (204) 0805 X7R,0805 200nF 204 X7R capacitor 100pcs,https://www.aliexpress.com/w/wholesale-0805-200nF-204-X7R-ca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,100,1.20,0.01,4.45,"Stage 3 45 Hz Butterworth LPF feedback capacitor (200nF preferred; 220nF shifts upper cutoff slightly to ~42 Hz)"
"C6,C7,C11,C12,C13",5,100nF 50V X7R 10%,0805,100nF (104) 0805 X7R,0805 100nF 104 X7R capacitor 100pcs,https://www.aliexpress.com/w/wholesale-0805-100nF-104-X7R-ca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,100,0.95,0.05,3.50,"LPF shunt (C6), ADC reservoir (C7), op-amp supply bypass (C11,C12), USB 5V LPF HF bypass (C13)"
"C8,C9,C10,C14,C15",5,10uF 25V X5R/X7R 10%,0805,10uF (106) 0805 25V,0805 10uF 106 25V capacitor 100pcs,https://www.aliexpress.com/w/wholesale-0805-10uF-106-25V-cap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,100,1.60,0.08,5.90,"Choose >=16V/25V rating to minimize DC bias capacitance drop; VREF filter (C8), USB 5V LPF (C9), +3V3_ANA LDO output (C10); op-amp filtered supplies (C14, C15)"
R1,1,1M Ohm 1% 1/8W,0805,1M (1004 / 01F) 0805 1%,0805 1M ohm 1% resistor 100pcs,https://www.aliexpress.com/w/wholesale-0805-1M-ohm-1%25-resi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,100,0.85,0.01,3.15,"Stage 1 high-impedance VREF input bias resistor"
"R2,R16,R17",3,220R (220 Ohm) 1% 1/8W,0805,220R (2200) 0805 1%,0805 220R 220 ohm 1% resistor 100pcs,https://www.aliexpress.com/w/wholesale-0805-220R-220-ohm-1%2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,100,0.85,0.03,3.15,"Stage 1 gain-setting resistor (R2 on F.Cu, G = 455.5 / 53.2 dB) + active-low LED current-limit resistors (R16, R17 on B.Cu, ~5.7-5.9 mA)"
"R4,R5,R6",3,100k Ohm 1% 1/8W,0805,100k (1003 / 01D) 0805 1%,0805 100K ohm 1% resistor 100pcs,https://www.aliexpress.com/w/wholesale-0805-100K-ohm-1%25-re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,100,0.85,0.03,3.15,"1% tolerance recommended so R5/R6 divider keeps VREF = 1.650V centered"
R7,1,22.6k Ohm 1% 1/8W (E96),0805,22.6k (2262 / 35C) 0805 1%,0805 22.6K 22K6 1% resistor 100pcs,https://www.aliexpress.com/w/wholesale-0805-22.6K-22K6-1%25-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,100,0.95,0.01,3.50,"E96 1% precision value for Stage 2 5 Hz Butterworth HPF (22k E24 substitute works in a pinch)"
R8,1,45.3k Ohm 1% 1/8W (E96),0805,45.3k (4532 / 64C) 0805 1%,0805 45.3K 45K3 1% resistor 100pcs,https://www.aliexpress.com/w/wholesale-0805-45.3K-45K3-1%25-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,100,0.95,0.01,3.50,"E96 1% precision value for Stage 2 5 Hz Butterworth HPF (47k E24 substitute shifts Q slightly)"
"R9,R10",2,24.9k Ohm 1% 1/8W (E96),0805,24.9k (2492 / 39C) 0805 1%,0805 24.9K 24K9 1% resistor 100pcs,https://www.aliexpress.com/w/wholesale-0805-24.9K-24K9-1%25-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,100,0.95,0.02,3.50,"E96 1% precision value for Stage 3 45 Hz Butterworth LPF (24k E24 substitute shifts fc to ~46.7 Hz)"
R11,1,100R (100 Ohm) 1% 1/8W,0805,100R (1000 / 01A) 0805 1%,0805 100R 100 ohm 1% resistor 100pcs,https://www.aliexpress.com/w/wholesale-0805-100R-100-ohm-1%2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,100,0.85,0.01,3.15,"RA4M1 14-bit SAR ADC anti-kickback isolation resistor"
R12,1,2.2k Ohm 1% 1/8W,0805,2.2k (2201 / 29B) 0805 1%,0805 2.2K 2K2 1% resistor 100pcs,https://www.aliexpress.com/w/wholesale-0805-2.2K-2K2-1%25-re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,100,0.85,0.01,3.15,"Electret microphone bias resistor (active only when JP1 solder jumper is bridged)"
"R13,R14,R15",3,10R (10 Ohm) 1% 1/8W,0805,10R (10R0 / 01X) 0805 1%,0805 10R 10 ohm 1% resistor 100pcs,https://www.aliexpress.com/w/wholesale-0805-10R-10-ohm-1%25-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,100,0.85,0.03,3.15,"USB +5V power-supply RC low-pass filter series resistor (fc = 1.58 kHz with C9 || C13); R14/R15 = per-op-amp supply RC filters"
LED2,1,Red LED 0805,0805,Red 0805 SMD LED (KT-0805R),0805 red SMD LED 100pcs,https://www.aliexpress.com/w/wholesale-0805-red-SMD-LED.html,100,,,,"Price not estimated yet. Vf ~2.0 V, mounted on B.Cu under XIAO (active-low via D8/SCK)"
LED1,1,Yellow-green LED 0805 (568-574 nm),0805,Yellow-green 0805 SMD LED (KT-0805YG),0805 yellow green SMD LED 570nm 100pcs,https://www.aliexpress.com/w/wholesale-0805-yellow-green-SMD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,100,,,,"Price not estimated yet. Yellow-green 568-574 nm (KT-0805YG / LCSC C2292), Vf ~2.0-2.2 V on B.Cu under XIAO (active-low via D7/RX). NOT pure/emerald green 520 nm (Vf ~3 V)"
"JP1,TP1-TP6,R3",0,Bare PCB Pads / DNP,PCB Copper,N/A,N/A,,0,0.00,0.00,0.00,"No purchase needed: JP1 is an SMD solder-bridge jumper on PCB copper; TP1-TP6 are SMD test pads; R3 is DNP"
TOTAL,39,Complete EarScope Rev 2.2 BOM (22 orderable lines),,,,https://www.aliexpress.com,,,,,"All resistors/capacitors/LEDs unified on 0805; cost totals not re-estimated for OPA2388IDR & LEDs"
